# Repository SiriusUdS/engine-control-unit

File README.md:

# kicad-template
template for KiCad PCB projects

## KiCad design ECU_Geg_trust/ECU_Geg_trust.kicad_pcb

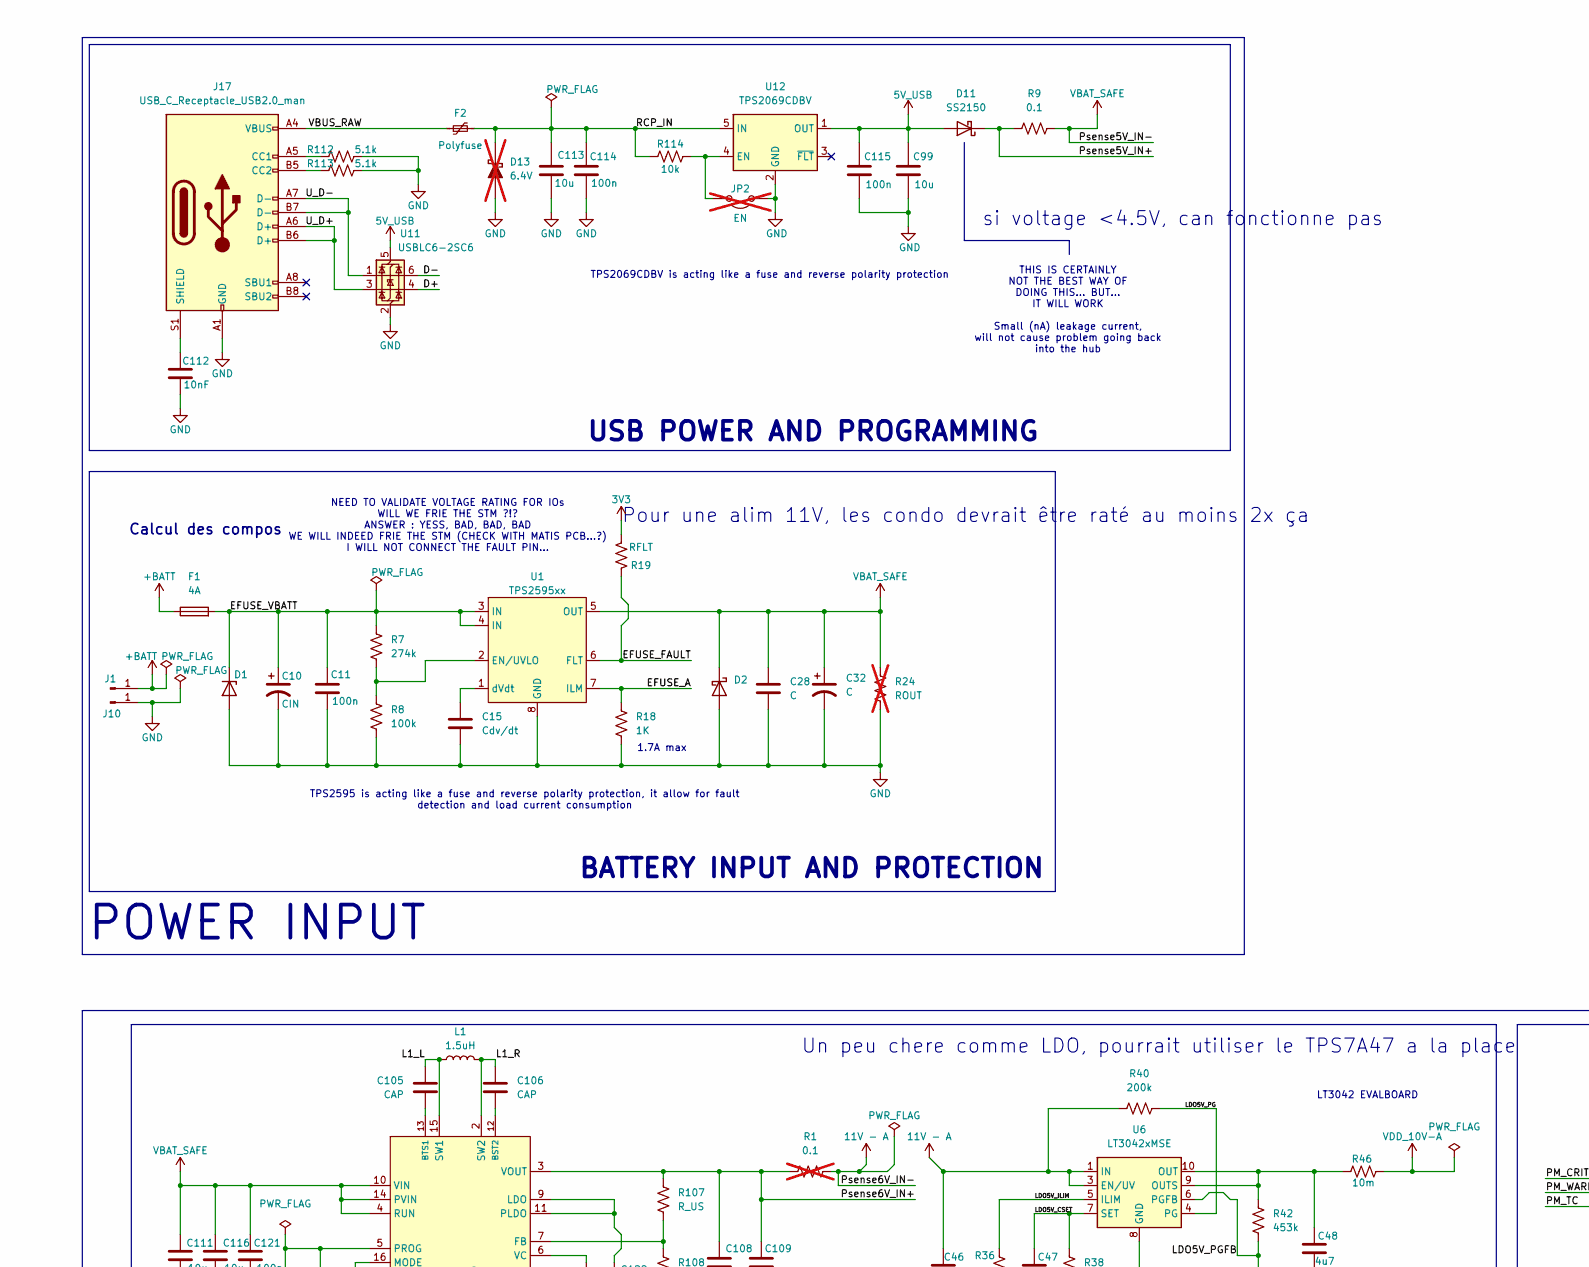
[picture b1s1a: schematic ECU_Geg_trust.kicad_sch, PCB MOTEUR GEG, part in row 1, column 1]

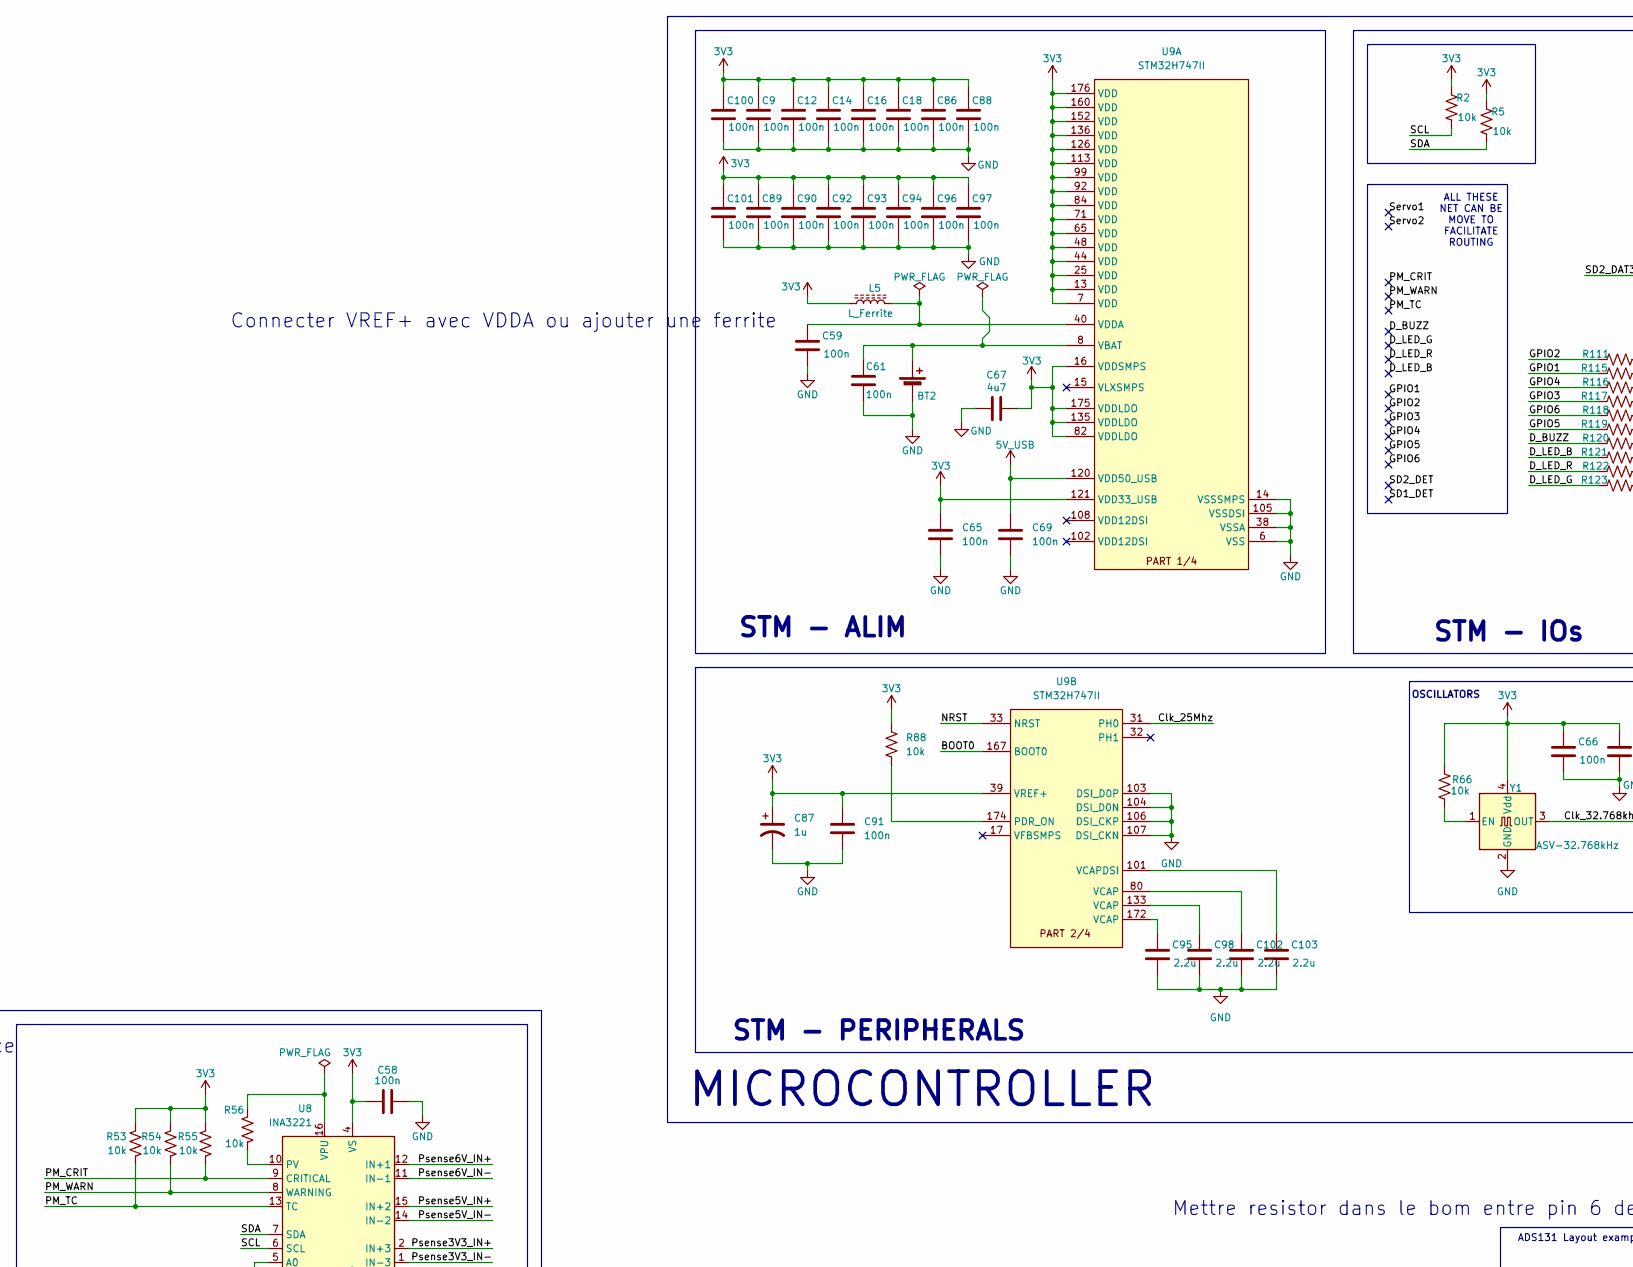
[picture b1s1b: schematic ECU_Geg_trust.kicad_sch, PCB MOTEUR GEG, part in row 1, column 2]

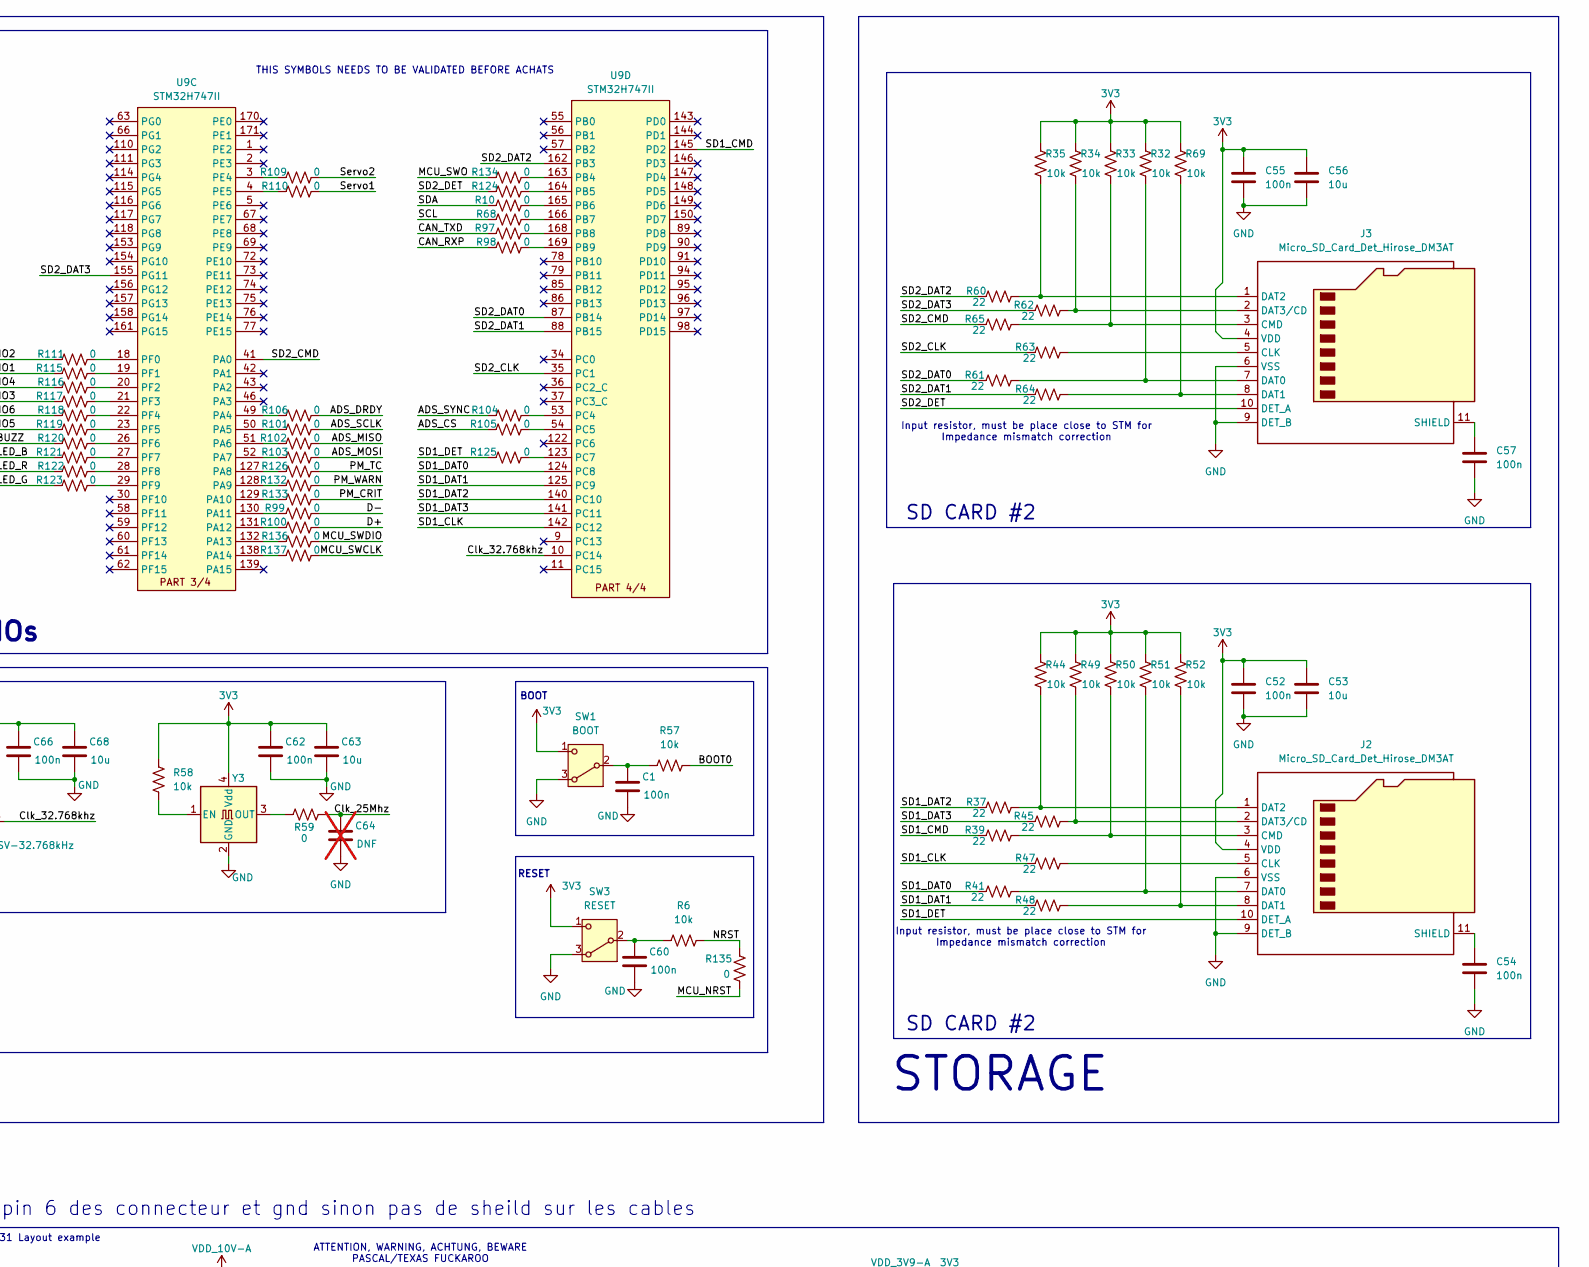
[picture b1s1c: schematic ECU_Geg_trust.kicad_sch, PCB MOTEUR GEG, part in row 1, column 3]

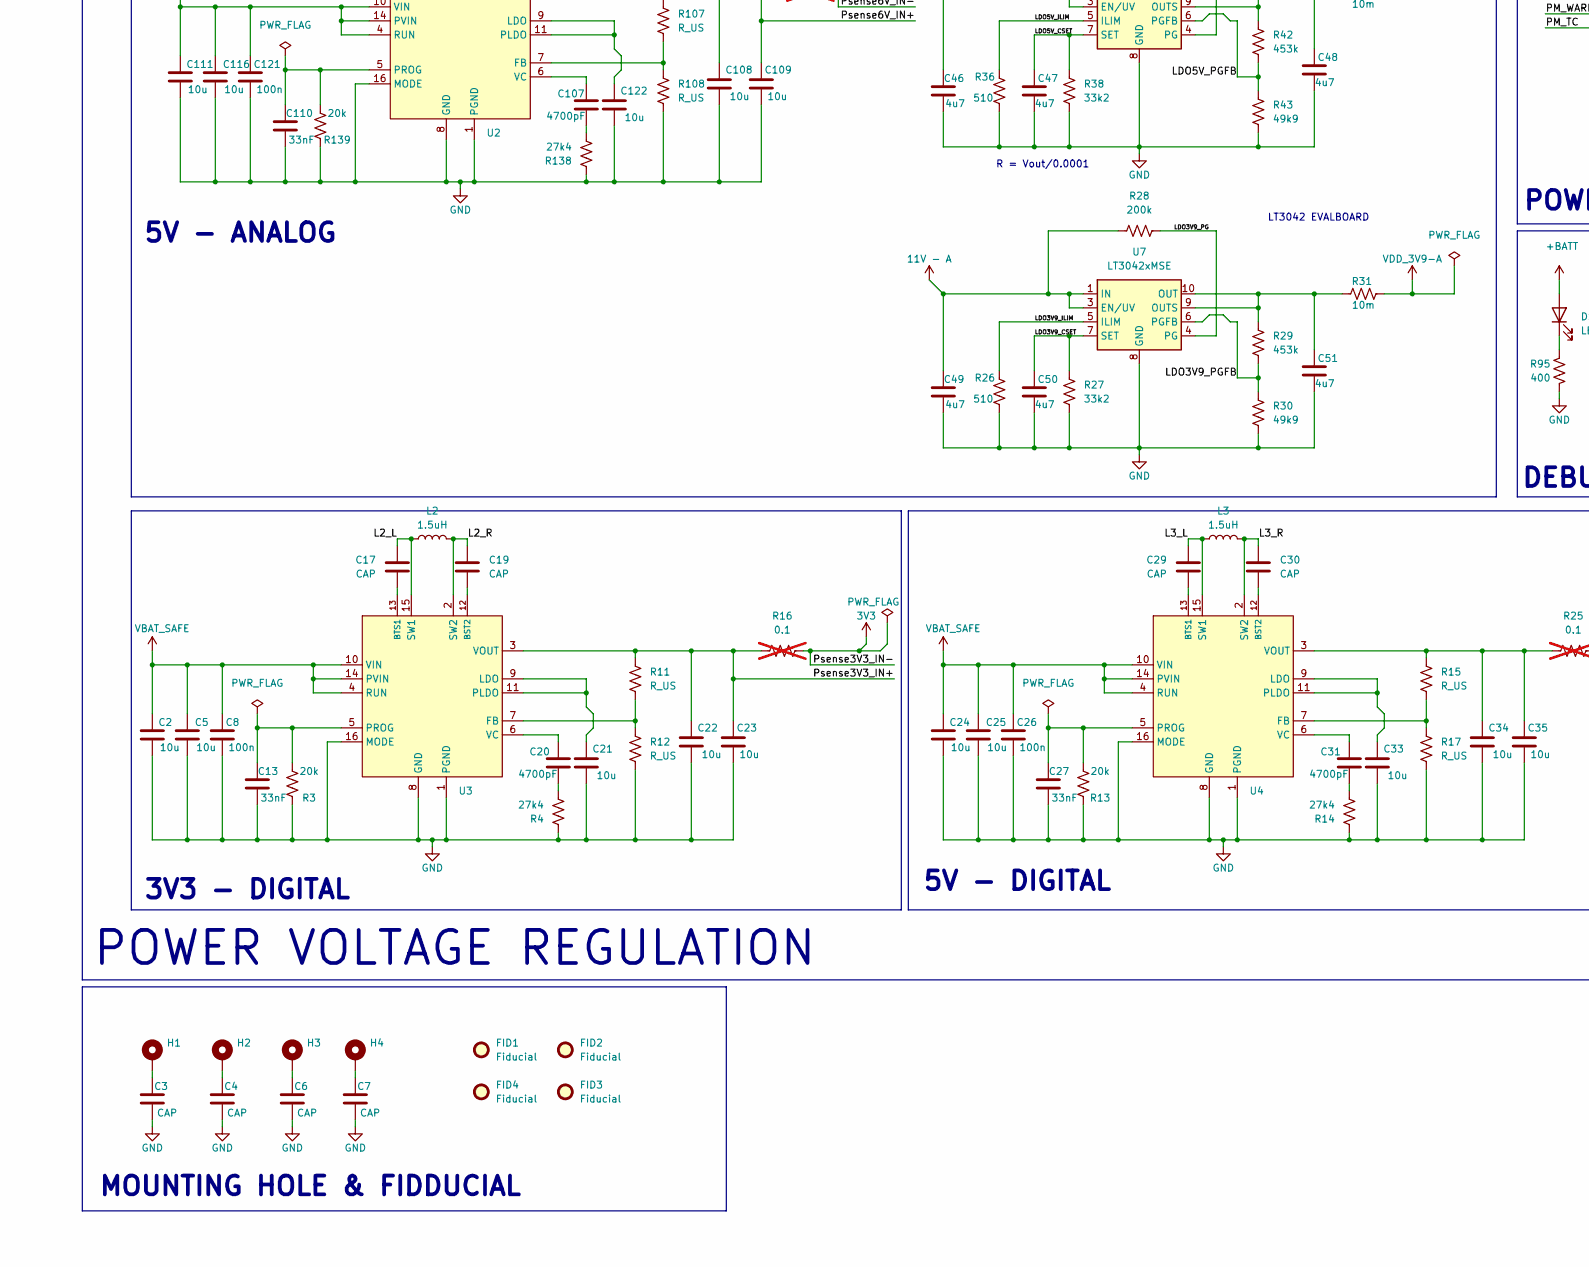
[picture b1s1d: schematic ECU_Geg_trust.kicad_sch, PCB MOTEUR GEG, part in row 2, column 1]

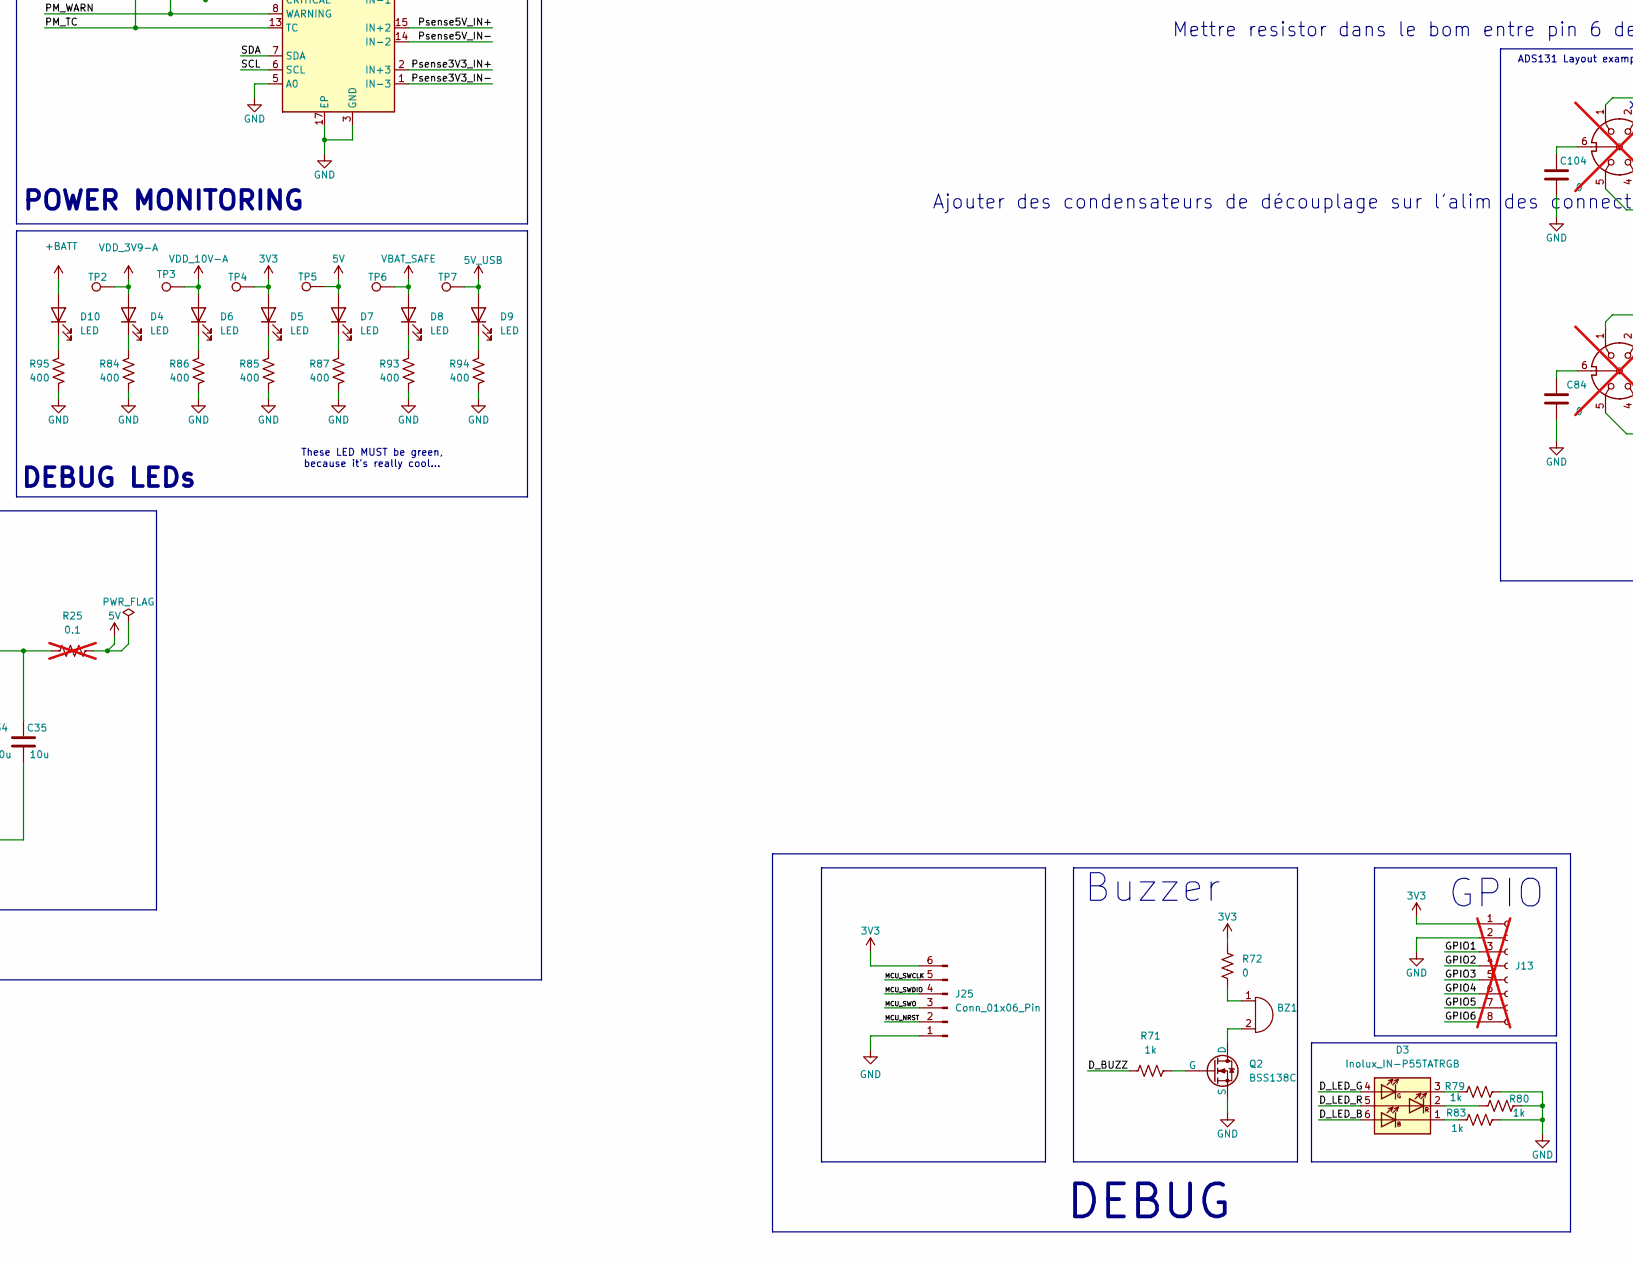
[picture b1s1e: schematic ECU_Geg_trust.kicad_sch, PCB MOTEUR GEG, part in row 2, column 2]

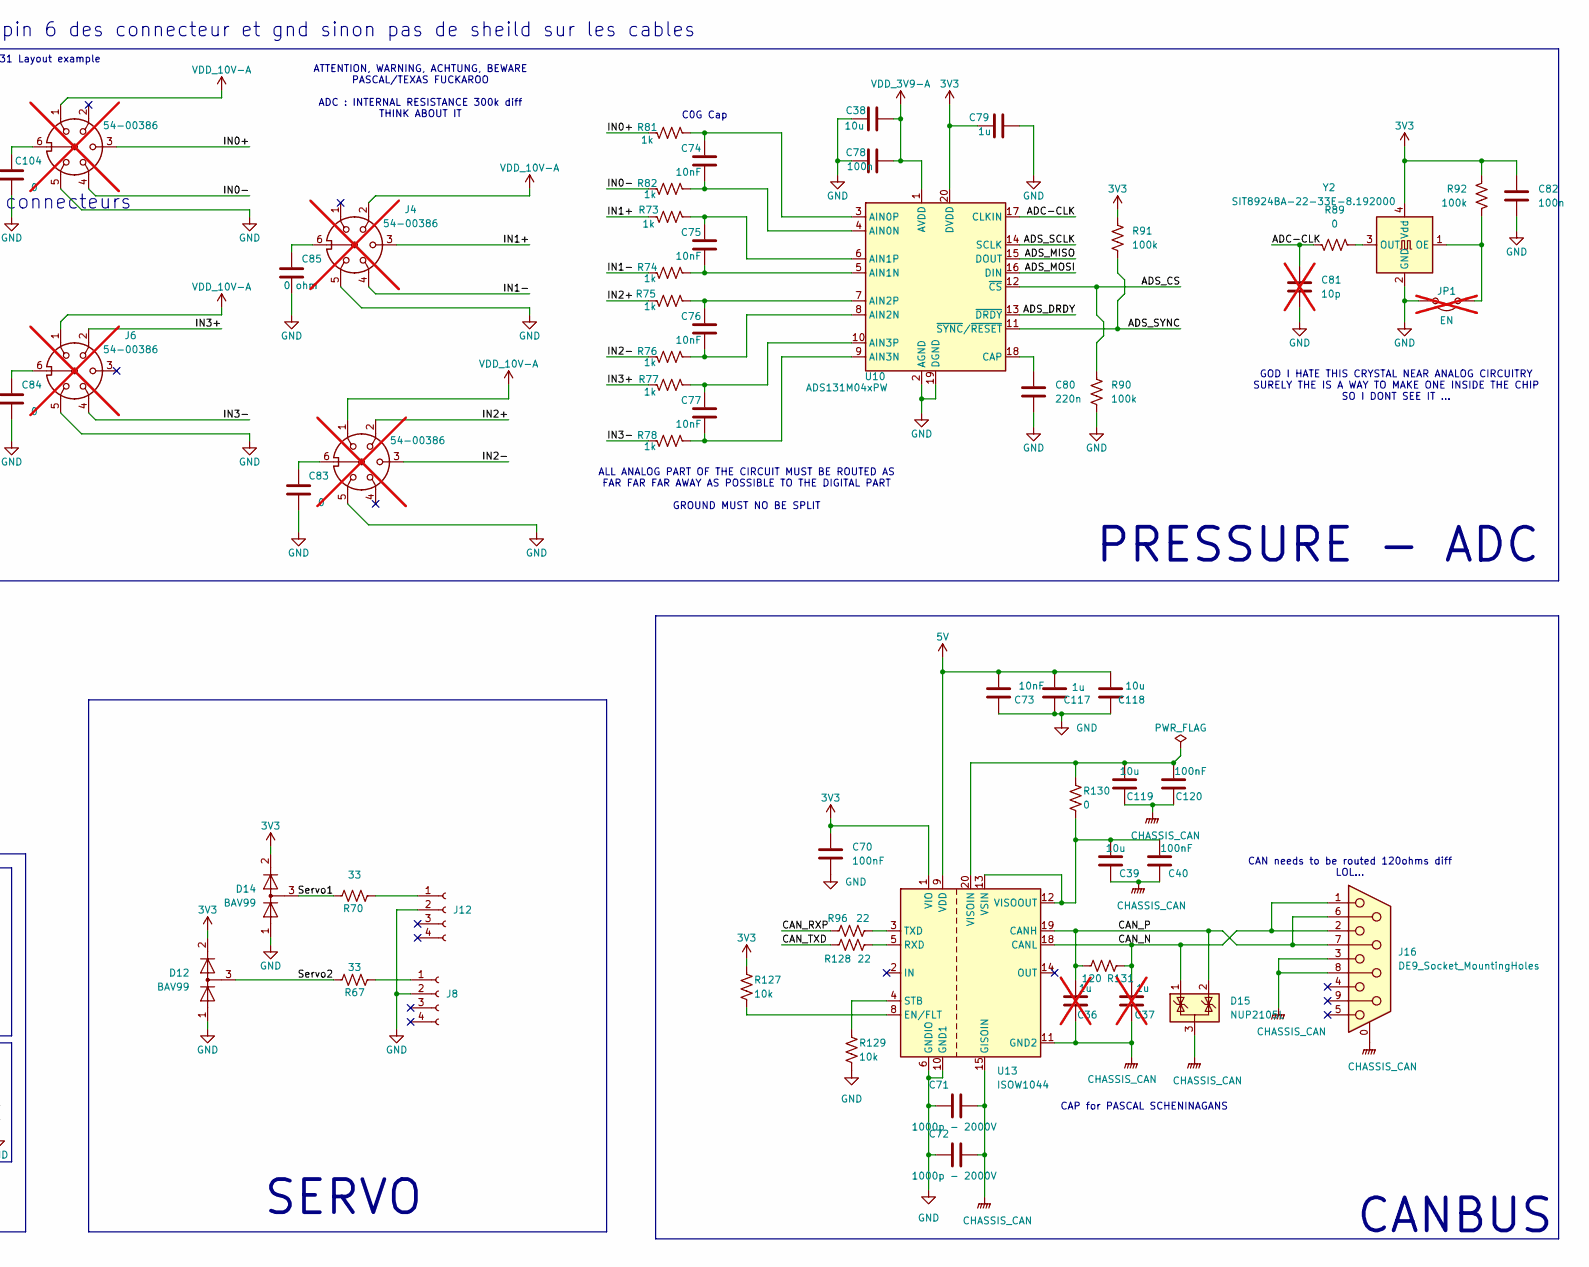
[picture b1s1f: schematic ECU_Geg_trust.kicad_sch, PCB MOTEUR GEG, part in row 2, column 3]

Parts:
BT2: Battery_Cell; BatteryHolder_Keystone_3000_1x12mm
BZ1: Buzzer_TDK_PS1240; Buzzer_Murata_PKMCS0909E; JLCP C910763
C1, C59, C60, C62, C65, C66, C69, C91: 100n; C_0402_1005Metric; JLCP C76997
C2, C23, C24, C35, C109, C111: 10u; C_1206_3216Metric; JLCP C1849
C3, C4, C6, C7, C17, C19, C29, C30, C105, C106: CAP; C_0402_1005Metric
C5, C21, C22, C25, C33, C34, C53, C56, C108, C116, C118, C122: 10u; C_0603_1608Metric; JLCP C70225
C8, C11, C26, C52, C54, C55, C57, C58, C61, C82, C121: 100n; C_0603_1608Metric; JLCP C1590
C9, C12, C14, C16, C18, C86, C88, C89, C90, C92, C93, C94, C96, C97, C100, C101, C114, C115: 100n; C_0402_1005Metric; Part Number 399-C0603C104K5RAC7411CT-ND; JLCP C76997
C10: CIN; CP_Elec_6.3x5.4
C13, C27, C110: 33nF; C_0402_1005Metric; JLCP C60425
C15: Cdv/dt; C_0603_1608Metric
C20, C31, C107: 4700pF; C_0402_1005Metric; JLCP C1538
C28: C; C_0603_1608Metric
C32: C; CP_Elec_6.3x5.4
C36, C37: 1u; C_0603_1608Metric; not fitted
C38: 10u; C_0805_2012Metric
C39, C119: 10u; C_0603_1608Metric; JLCP C1592
C40, C70, C120: 100nF; C_0603_1608Metric; JLCP C1590
C46, C47, C48, C49, C50, C51: 4u7; C_1206_3216Metric; JLCP C1872
C63, C68: 10u; C_0402_1005Metric; JLCP C77000
C64: DNF; C_0402_1005Metric; not fitted
C67: 4u7; C_0603_1608Metric; JLCP C23733
C71, C72: 1000p - 2000V; C_1210_3225Metric; JLCP C9196
C73, C74, C75, C76, C77, C112: 10nF; C_0603_1608Metric; JLCP C1589
C78: 100n; C_0603_1608Metric
C79, C117: 1u; C_0603_1608Metric; JLCP C1592
C80: 220n; C_0603_1608Metric; JLCP C1606
C81: 10p; C_0402_1005Metric; not fitted
C83, C84, C104: 0; C_0402_1005Metric; JLCP C17168
C85: 0 ohm; C_0402_1005Metric; JLCP C17168
C87: 1u; C_0402_1005Metric
C95, C98, C102, C103: 2.2u; C_0603_1608Metric; JLCP C23630
C99: 10u; C_0805_2012Metric; Part Number 399-C0603C104K5RAC7411CT-ND
C113: 10u; C_0603_1608Metric; Part Number 399-C0603C104K5RAC7411CT-ND; LCSC C1713
D1: SMBJ16A-13-F; D_SMB; JLCP C5353262
D2: MBR130T1G; D_SOD-123; JLCP C82461
D3: Inolux_IN-P55TATRGB; LED_Inolux_IN-P55TATRGB_PLCC6_5.0x5.5mm_P1.8mm; JLCP C5656598
D4, D5, D6, D7, D8, D9, D10: LED; LED_0603_1608Metric; JLCP C2286
D11: SS2150; D_SMA; JLCP C2891715
D12, D14: BAV99; SOT-23; JLCP C2500
D13: 6.4V; D_0603_1608Metric_Pad1.05x0.95mm_HandSolder; Part Number 1727-7327-1-ND; not fitted
D15: NUP2105L; SOT-23; JLCP C14486
F1: 4A; Fuse_0805_2012Metric; JLCP C187606
F2: Polyfuse; Fuse_0603_1608Metric_Pad1.05x0.95mm_HandSolder; Part Number 13-SMD0603B050TFCT-ND
FID1, FID2, FID3, FID4: Fiducial; Fiducial_0.5mm_Mask1mm
H1, H2, H3, H4: MountingHole_Pad; MountingHole_3.2mm_M3_DIN965_Pad_TopBottom
J1, J10: Conn_01x01_Pin; Wuerth_REDCUBE-THR_WP-THRBU_74650174_THR
J2, J3: Micro_SD_Card_Det_Hirose_DM3AT; microSD_HC_Hirose_DM3AT-SF-PEJM5; JLCP C114218
J4, J5, J7: 54-00386; not fitted
J6: 54-00386; JLCP C17168; not fitted
J8, J12: Conn_01x04_Socket; CUSTOM_CONN_1723102000_02_MOL
J13: Conn_01x08_Socket; PinHeader_2x04_P2.54mm_Vertical; not fitted
J16: DE9_Socket_MountingHoles; DSUB-9_Socket_Horizontal_P2.77x2.84mm_EdgePinOffset4.94mm_H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; JLCP C183530
J17: USB_C_Receptacle_USB2.0_man; USB_C_Receptacle_GCT_USB4105-xx-A_16P_TopMnt_Horizontal; Part Number 2073-USB4105-GF-ACT-ND; JLCP C5184243
J25: Conn_01x06_Pin; CUSTOM_Conn_JTAG
JP1, JP2: EN; C_0402_1005Metric; not fitted
L1, L2, L3: 1.5uH; CUSTOM_BMRA000606301R5MA1; JLCP C2936659 ps sur
L5: L_Ferrite; R_0402_1005Metric
Q2: BSS138C; TSOT-23_HandSoldering; JLCP C255592
R1, R16, R25: 0.1; R_0402_1005Metric; not fitted
R2, R5, R32, R33, R34, R35, R44, R49, R50, R51, R52, R53, R54, R55, R56, R69: 10k; R_0402_1005Metric; JLCP C25531
R3, R13, R139: 20k; R_0402_1005Metric; JLCP C25545
R4, R14, R138: 27k4; R_0402_1005Metric; JLCP C26971
R6, R57, R88, R127, R129: 10k; R_0603_1608Metric_Pad0.98x0.95mm_HandSolder; JLCP C15401
R7: 274k; R_0603_1608Metric
R8: 100k; R_0603_1608Metric
R9: 0.1; R_0402_1005Metric; JLCP C158960
R10, R59, R68, R89, R97, R98, R99, R100, R101, R102, R103, R104, R105, R106, R109, R110, R111, R115, R116, R117, R118, R119, R120, R121, R122, R123, R124, R125, R126, R132, R133, R134, R136, R137: 0; R_0402_1005Metric; JLCP C17168
R11, R12, R15, R17, R107, R108: R_US; R_0603_1608Metric
R18: 1K; R_0603_1608Metric
R19: RFLT; R_0603_1608Metric
R24: ROUT; R_0603_1608Metric; not fitted
R26, R36: 510; R_0603_1608Metric; JLCP C23193
R27, R38: 33k2; R_0603_1608Metric; JLCP C23003
R28, R40: 200k; R_0402_1005Metric; JLCP C25544
R29, R42: 453k; R_0603_1608Metric; JLCP C25818
R30, R43: 49k9; R_0603_1608Metric; JLCP C23184
R31, R46: 10m; R_0603_1608Metric; JLCP C156369
R37, R39, R41, R45, R47, R48, R60, R61, R62, R63, R64, R65, R96, R128: 22; R_0402_1005Metric; JLCP C159964
R58, R66: 10k; C_0402_1005Metric; JLCP C25531
R67, R70: 33; C_0603_1608Metric; JLCP C113041 ps sur
R71, R73, R74, R75, R76, R77, R78, R79, R80, R81, R82, R83: 1k; R_0603_1608Metric; JLCP C14676
R72: 0; R_0603_1608Metric; JLCP C15402
R84, R85, R86, R87, R93, R94, R95: 400; R_0402_1005Metric
R90, R91, R92: 100k; R_0402_1005Metric; JLCP C25530
R112, R113: 5.1k; R_0402_1005Metric; JLCP C25905
R114: 10k; R_0603_1608Metric; JLCP C15401
R130, R135: 0; R_0603_1608Metric_Pad0.98x0.95mm_HandSolder; JLCP C15402
R131: 120; R_0603_1608Metric_Pad0.98x0.95mm_HandSolder; JLCP C22787
SW1: BOOT; Nidec_Copal_CAS-120A; JLCP C2921537
SW3: RESET; Nidec_Copal_CAS-120A; JLCP C2921537
TP2, TP3, TP4, TP5, TP6, TP7: TestPoint; TestPoint_Pad_D2.5mm
U1: TPS2595xx; WSON-8-1EP_2x2mm_P0.5mm_EP0.9x1.6mm; JLCP C471038
U2, U3, U4: HTSSOP-16-1EP_4.4x5mm_P0.65mm_EP3.4x5mm_Mask2.46x2.31mm_The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; JLCP C580684 vr ps sur
U6, U7: LT3042xMSE; MSOP-10-1EP_3x3mm_P0.5mm_EP1.68x1.88mm
U8: INA3221; Texas_RGV0016A_VQFN-16-1EP_4x4mm_P0.65mm_EP2.1x2.1mm; JLCP C181255
U9: STM32H747II; LQFP-176_24x24mm_P0.5mm; JLCP C730199
U10: ADS131M04xPW; TSSOP-20_4.4x6.5mm_P0.65mm; JLCP C2862562
U11: USBLC6-2SC6; SOT-23-6; Part Number 497-5235-1-ND; JLCP C7519
U12: TPS2069CDBV; SOT-23-5; JLCP C181752
U13: ISOW1044; SOIC-20W_7.5x12.8mm_P1.27mm; JLCP C5216545
Y1: ASV-32.768kHz; Oscillator_SMD_Abracon_ASV-4Pin_7.0x5.1mm; JLCP ??
Y2: SIT8924BA-22-33E-8.192000; Oscillator_SMD_SiT_PQFN-4Pin_3.2x2.5mm; JLCP C7496633
Y3: ASV-25.000MHz; Oscillator_SMD_Abracon_ASV-4Pin_7.0x5.1mm; JLCP ??

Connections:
3V3: C9.1, C12.1, C14.1, C16.1, C18.1, C52.1, C53.1, C55.1, C56.1, C58.1, C62.1, C63.1, C65.1, C66.1, C67.2, C68.1, C70.1, C79.1, C82.2, C86.1, C87.1, C88.1, C89.1, C90.1, C91.1, C92.1, C93.1, C94.1, C96.1, C97.1, C100.1, C101.1, D5.2 (A), D12.2 (A), D14.2 (A), J2.4 (VDD), J3.4 (VDD), J13.1, J25.6, L5.1, R2.1, R5.1, R16.2, R19.2, R32.1, R33.1, R34.1, R35.1, R44.1, R49.1, R50.1, R51.1, R52.1, R53.1, R54.1, R55.1, R58.1, R66.1, R69.1, R72.1, R88.1, R91.1, R92.1, R127.1, SW1.1 (C), SW3.1 (C), TP4.1, U8.1 (IN-3), U8.4 (VS), U9.7 (VDD), U9.13 (VDD), U9.16 (VDDSMPS), U9.25 (VDD), U9.39 (VREF+), U9.44 (VDD), U9.48 (VDD), U9.65 (VDD), U9.71 (VDD), U9.82 (VDDLDO), U9.84 (VDD), U9.92 (VDD), U9.99 (VDD), U9.113 (VDD), U9.121 (VDD33_USB), U9.126 (VDD), U9.135 (VDDLDO), U9.136 (VDD), U9.152 (VDD), U9.160 (VDD), U9.175 (VDDLDO), U9.176 (VDD), U10.20 (DVDD), U13.1 (VIO), Y1.4 (Vdd), Y2.4 (Vdd), Y3.4 (Vdd)
5V: C73.2, C117.2, C118.2, D7.2 (A), R25.2, TP5.1, U13.9 (VDD)
5V_USB: C69.1, C99.1, C115.1, D9.2 (A), D11.2 (A), TP7.1, U9.120 (VDD50_USB), U11.5 (VBUS), U12.1 (OUT)
6V - A: C46.1, C49.1, R1.2, R28.1, R40.1, U6.1 (IN), U6.2 (IN), U6.3 (EN/UV), U7.1 (IN), U7.2 (IN), U7.3 (EN/UV), U8.11 (IN-1)
+BATT: D10.2 (A), F1.1, J1.1
/ADC-CLK: C81.2, R89.1, U10.17 (CLKIN)
/ADS_CS: R90.1, R105.1, U10.12 (~CS)
/ADS_DRDY: R106.2, U10.13 (~DRDY)
/ADS_MISO: R102.2, U10.15 (DOUT)
/ADS_MOSI: R103.2, U10.16 (DIN)
/ADS_SCLK: R101.2, U10.14 (SCLK)
/ADS_SYNC: R91.2, R104.1, U10.11 (~SYNC/~RESET)
/BOOT0: R57.2, U9.167 (BOOT0)
/CAN_N: C37.2, D15.1 (K), J16.1, J16.2, R131.1, U13.18 (CANL)
/CAN_P: C36.2, D15.2 (K), J16.6, J16.7, R131.2, U13.19 (CANH)
/CAN_RXP: R96.1, R98.1
/CAN_TXD: R97.1, R128.1
/Clk_25Mhz: C64.1, R59.2, U9.31 (PH0)
/Clk_32.768khz: U9.10 (PC14), Y1.3 (OUT)
/D+: R100.2, U11.4 (I/O2)
/D-: R99.2, U11.6 (I/O1)
/D_BUZZ: R71.1, R120.1
/D_LED_B: D3.6 (AB), R121.1
/D_LED_G: D3.4 (AG), R123.1
/D_LED_R: D3.5 (AR), R122.1
/EFUSE_A: R18.1, U1.7 (ILM)
/EFUSE_FAULT: R19.1, U1.6 (FLT)
/EFUSE_VBATT: C10.1, C11.1, D1.1 (K), F1.2, R7.1, U1.3 (IN), U1.4 (IN)
/GPIO1: J13.3, R115.1
/GPIO2: J13.4, R111.1
/GPIO3: J13.5, R117.1
/GPIO4: J13.6, R116.1
/GPIO5: J13.7, R119.1
/GPIO6: J13.8, R118.1
/IN0+: J5.3, R81.2
/IN0-: J5.4, R82.2
/IN1+: J4.3, R73.2
/IN1-: J4.4, R74.2
/IN2+: J7.2, R75.2
/IN2-: J7.3, R76.2
/IN3+: J6.2, R77.2
/IN3-: J6.4, R78.2
/L1_L: C105.1, L1.1, U2.15 (SW1)
/L1_R: C106.1, L1.2, U2.2 (SW2)
/L2_L: C17.1, L2.1, U3.15 (SW1)
/L2_R: C19.1, L2.2, U3.2 (SW2)
/L3_L: C29.1, L3.1, U4.15 (SW1)
/L3_R: C30.1, L3.2, U4.2 (SW2)
/LDO3V9_CSET: C50.1, R27.1, U7.7 (SET)
/LDO3V9_ILIM: R26.1, U7.5 (ILIM)
/LDO3V9_PG: R28.2, U7.4 (PG)
/LDO3V9_PGFB: R29.2, R30.1, U7.6 (PGFB)
/LDO5V_CSET: C47.1, R38.1, U6.7 (SET)
/LDO5V_ILIM: R36.1, U6.5 (ILIM)
/LDO5V_PG: R40.2, U6.4 (PG)
/LDO5V_PGFB: R42.2, R43.1, U6.6 (PGFB)
/MCU_NRST: J25.2, R135.1
/MCU_SWCLK: J25.5, R137.2
/MCU_SWDIO: J25.4, R136.2
/MCU_SWO: J25.3, R134.1
/NRST: R6.2, R135.2, U9.33 (NRST)
/PM_CRIT: R55.2, R133.2, U8.9 (CRITICAL)
/PM_TC: R53.2, R126.2, U8.13 (TC)
/PM_WARN: R54.2, R132.2, U8.8 (WARNING)
/Psense3V3_IN+: C22.1, C23.1, R11.1, R16.1, U3.3 (VOUT), U8.2 (IN+3)
/Psense5V_IN+: D11.1 (K), R9.1, U8.15 (IN+2)
/Psense6V_IN+: C108.1, C109.1, R1.1, R107.1, U2.3 (VOUT), U8.12 (IN+1)
/RCP_IN: C113.1, C114.1, D13.1 (K), F2.2, R114.1, U12.5 (IN)
/SCL: R2.2, R68.1, U8.6 (SCL)
/SD1_CLK: R47.1, U9.142 (PC12)
/SD1_CMD: R39.1, U9.145 (PD2)
/SD1_DAT0: R41.1, U9.124 (PC8)
/SD1_DAT1: R48.1, U9.125 (PC9)
/SD1_DAT2: R37.1, U9.140 (PC10)
/SD1_DAT3: R45.1, U9.141 (PC11)
/SD1_DET: J2.10 (DET_A), R125.1
/SD2_CLK: R63.1, U9.35 (PC1)
/SD2_CMD: R65.1, U9.41 (PA0)
/SD2_DAT0: R61.1, U9.87 (PB14)
/SD2_DAT1: R64.1, U9.88 (PB15)
/SD2_DAT2: R60.1, U9.162 (PB3)
/SD2_DAT3: R62.1, U9.155 (PG11)
/SD2_DET: J3.10 (DET_A), R124.1
/SDA: R5.2, R10.1, U8.7 (SDA)
/Servo1: D14.3 (K), R70.1, R110.2
/Servo2: D12.3 (K), R67.2, R109.2
/U_D+: J17.A6 (D+), J17.B6 (D+), U11.3 (I/O2)
/U_D-: J17.A7 (D-), J17.B7 (D-), U11.1 (I/O1)
/VBUS_RAW: F2.1, J17.A4 (VBUS), J17.A9 (VBUS), J17.B4 (VBUS), J17.B9 (VBUS)
CHASSIS_CAN: C36.1, C37.1, C39.1, C40.1, C71.2, C72.2, C119.1, C120.1, D15.3 (A), J16.0 (PAD), J16.3, J16.8, U13.11 (GND2), U13.15 (GISOIN), U13.16 (GISOIN), U13.17 (GISOIN)
GND: BT2.2 (-), C1.2, C2.2, C3.2, C4.2, C5.2, C6.2, C7.2, C8.2, C9.2, C10.2, C11.2, C12.2, C13.2, C14.2, C15.2, C16.2, C18.2, C21.2, C22.2, C23.2, C24.2, C25.2, C26.2, C27.2, C28.2, C32.2, C33.2, C34.2, C35.2, C38.1, C46.2, C47.2, C48.2, C49.2, C50.2, C51.2, C52.2, C53.2, C54.2, C55.2, C56.2, C57.2, C58.2, C59.2, C60.2, C61.1, C62.2, C63.2, C64.2, C65.2, C66.2, C67.1, C68.2, C69.2, C70.2, C71.1, C72.1, C73.1, C78.1, C79.2, C80.1, C81.1, C82.1, C83.2, C84.2, C85.2, C86.2, C87.2, C88.2, C89.2, C90.2, C91.2, C92.2, C93.2, C94.2, C95.2, C96.2, C97.2, C98.2, C99.2, C100.2, C101.2, C102.2, C103.2, C104.2, C108.2, C109.2, C110.2, C111.2, C112.2, C113.2, C114.2, C115.2, C116.2, C117.1, C118.1, C121.2, C122.2, D1.2 (A), D2.2 (A), D12.1 (K), D13.2 (A), D14.1 (K), J2.6 (VSS), J2.9 (DET_B), J3.6 (VSS), J3.9 (DET_B), J4.5, J5.5, J6.5, J7.5, J8.2, J10.1, J12.2, J13.2, J17.A1 (GND), J17.A12 (GND), J17.B1 (GND), J17.B12 (GND), J25.1, JP1.1 (A), JP2.1 (A), Q2.3 (S), R3.1, R4.1, R8.2, R12.2, R13.1, R14.1, R17.2, R18.2, R24.2, R26.2, R27.2, R30.2, R36.2, R38.2, R43.2, R79.2, R80.2, R83.2, R84.2, R85.2, R86.2, R87.2, R90.2, R93.2, R94.2, R95.2, R108.2, R112.1, R113.2, R129.2, R138.1, R139.1, SW1.3 (A), SW3.3 (A), U1.8 (GND), U1.9 (GND), U2.1 (PGND), U2.8 (GND), U2.16 (MODE), U3.1 (PGND), U3.8 (GND), U3.16 (MODE), U4.1 (PGND), U4.8 (GND), U4.16 (MODE), U6.8 (GND), U6.11 (GND), U7.8 (GND), U7.11 (GND), U8.3 (GND), U8.5 (A0), U8.17 (EP), U9.6 (VSS), U9.12 (VSS), U9.14 (VSSSMPS), U9.24 (VSS), U9.38 (VSSA), U9.45 (VSS), U9.47 (VSS), U9.64 (VSS), U9.70 (VSS), U9.81 (VSS), U9.83 (VSS), U9.93 (VSS), U9.100 (VSS), U9.103 (DSI_D0P), U9.104 (DSI_D0N), U9.105 (VSSDSI), U9.106 (DSI_CKP), U9.107 (DSI_CKN), U9.109 (VSSDSI), U9.112 (VSS), U9.119 (VSS), U9.134 (VSS), U9.137 (VSS), U9.151 (VSS), U9.159 (VSS), U9.173 (VSS), U10.2 (AGND), U10.19 (DGND), U11.2 (GND), U12.2 (GND), U13.6 (GNDIO), U13.10 (GND1), Y1.2 (GND), Y2.2 (GND), Y3.2 (GND)
unnamed: BT2.1 (+), C61.2, U9.8 (VBAT)
unnamed: BZ1.1, R72.2
unnamed: C3.1, H1.1
unnamed: C4.1, H2.1
unnamed: C6.1, H3.1
unnamed: C7.1, H4.1
unnamed: C20.1, R4.2
unnamed: C31.1, R14.2
unnamed: C83.1, J7.6, J7.SH
unnamed: C84.1, J6.6, J6.SH
unnamed: C85.1, J4.6, J4.SH
unnamed: C95.1, U9.172 (VCAP)
unnamed: C98.1, U9.133 (VCAP)
unnamed: C102.1, U9.80 (VCAP)
unnamed: C104.1, J5.6, J5.SH
unnamed: C107.1, R138.2
unnamed: D3.1 (KB), R83.1
unnamed: D3.3 (KG), R79.1
unnamed: D3.2 (KR), R80.1
unnamed: D4.1 (K), R84.1
unnamed: D5.1 (K), R85.1
unnamed: D6.1 (K), R86.1
unnamed: D7.1 (K), R87.1
unnamed: D8.1 (K), R93.1
unnamed: D9.1 (K), R94.1
unnamed: D10.1 (K), R95.1
unnamed: J2.5 (CLK), R47.2
unnamed: J2.3 (CMD), R39.2, R50.2
unnamed: J2.7 (DAT0), R41.2, R51.2
unnamed: J2.8 (DAT1), R48.2, R52.2
unnamed: J2.1 (DAT2), R37.2, R44.2
unnamed: J2.2 (DAT3/CD), R45.2, R49.2
unnamed: C54.1, J2.11 (SHIELD)
unnamed: J3.5 (CLK), R63.2
unnamed: J3.3 (CMD), R33.2, R65.2
unnamed: J3.7 (DAT0), R32.2, R61.2
unnamed: J3.8 (DAT1), R64.2, R69.2
unnamed: J3.1 (DAT2), R35.2, R60.2
unnamed: J3.2 (DAT3/CD), R34.2, R62.2
unnamed: C57.1, J3.11 (SHIELD)
unnamed: J8.1, R67.1
unnamed: J12.1, R70.2
unnamed: J17.A5 (CC1), R112.2
unnamed: J17.B5 (CC2), R113.1
unnamed: C112.1, J17.S1 (SHIELD)
unnamed: JP1.2 (B), R92.2, Y2.1 (OE)
unnamed: JP2.2 (B), R114.2, U12.4 (EN)
unnamed: BZ1.2, Q2.1 (D)
unnamed: Q2.2 (G), R71.2
unnamed: C1.1, R57.1, SW1.2 (B)
unnamed: C60.1, R6.1, SW3.2 (B)
unnamed: R7.2, R8.1, U1.2 (EN/UVLO)
unnamed: C15.1, U1.1 (dVdt)
unnamed: C106.2, U2.12 (BST2)
unnamed: C105.2, U2.13 (BTS1)
unnamed: R107.2, R108.1, U2.7 (FB)
unnamed: C122.1, U2.9 (LDO), U2.11 (PLDO)
unnamed: C110.1, R139.2, U2.5 (PROG)
unnamed: C107.2, U2.6 (VC)
unnamed: C19.2, U3.12 (BST2)
unnamed: C17.2, U3.13 (BTS1)
unnamed: R11.2, R12.1, U3.7 (FB)
unnamed: C21.1, U3.9 (LDO), U3.11 (PLDO)
unnamed: C13.1, R3.2, U3.5 (PROG)
unnamed: C20.2, U3.6 (VC)
unnamed: C30.2, U4.12 (BST2)
unnamed: C29.2, U4.13 (BTS1)
unnamed: R15.2, R17.1, U4.7 (FB)
unnamed: C33.1, U4.9 (LDO), U4.11 (PLDO)
unnamed: C27.1, R13.2, U4.5 (PROG)
unnamed: C31.2, U4.6 (VC)
unnamed: C34.1, C35.1, R15.1, R25.1, U4.3 (VOUT)
unnamed: C48.1, R42.1, R46.1, U6.9 (OUTS), U6.10 (OUT)
unnamed: C51.1, R29.1, R31.1, U7.9 (OUTS), U7.10 (OUT)
unnamed: R56.2, U8.10 (PV)
unnamed: R56.1, U8.16 (VPU)
unnamed: C59.1, L5.2, U9.40 (VDDA)
unnamed: R88.2, U9.174 (PDR_ON)
unnamed: C103.1, U9.101 (VCAPDSI)
unnamed: R106.1, U9.49 (PA4)
unnamed: R101.1, U9.50 (PA5)
unnamed: R102.1, U9.51 (PA6)
unnamed: R103.1, U9.52 (PA7)
unnamed: R126.1, U9.127 (PA8)
unnamed: R132.1, U9.128 (PA9)
unnamed: R133.1, U9.129 (PA10)
unnamed: R99.1, U9.130 (PA11)
unnamed: R100.1, U9.131 (PA12)
unnamed: R136.1, U9.132 (PA13)
unnamed: R137.1, U9.138 (PA14)
unnamed: R109.1, U9.3 (PE4)
unnamed: R110.1, U9.4 (PE5)
unnamed: R111.2, U9.18 (PF0)
unnamed: R115.2, U9.19 (PF1)
unnamed: R116.2, U9.20 (PF2)
unnamed: R117.2, U9.21 (PF3)
unnamed: R118.2, U9.22 (PF4)
unnamed: R119.2, U9.23 (PF5)
unnamed: R120.2, U9.26 (PF6)
unnamed: R121.2, U9.27 (PF7)
unnamed: R122.2, U9.28 (PF8)
unnamed: R123.2, U9.29 (PF9)
unnamed: R134.2, U9.163 (PB4)
unnamed: R124.2, U9.164 (PB5)
unnamed: R10.2, U9.165 (PB6)
unnamed: R68.2, U9.166 (PB7)
unnamed: R97.2, U9.168 (PB8)
unnamed: R98.2, U9.169 (PB9)
unnamed: R104.2, U9.53 (PC4)
unnamed: R105.2, U9.54 (PC5)
unnamed: R125.2, U9.123 (PC7)
unnamed: C74.1, R82.1, U10.4 (AIN0N)
unnamed: C74.2, R81.1, U10.3 (AIN0P)
unnamed: C75.1, R74.1, U10.5 (AIN1N)
unnamed: C75.2, R73.1, U10.6 (AIN1P)
unnamed: C76.1, R76.1, U10.8 (AIN2N)
unnamed: C76.2, R75.1, U10.7 (AIN2P)
unnamed: C77.1, R78.1, U10.9 (AIN3N)
unnamed: C77.2, R77.1, U10.10 (AIN3P)
unnamed: C80.2, U10.18 (CAP)
unnamed: R127.2, U13.8 (EN/FLT)
unnamed: R128.2, U13.5 (RXD)
unnamed: R129.1, U13.4 (STB)
unnamed: R96.2, U13.3 (TXD)
unnamed: C119.2, C120.2, R130.1, U13.20 (VISOIN)
unnamed: C39.2, C40.2, R130.2, U13.12 (VISOOUT), U13.13 (VSIN)
unnamed: R66.2, Y1.1 (EN)
unnamed: R89.2, Y2.3 (OUT)
unnamed: R58.2, Y3.1 (EN)
unnamed: R59.1, Y3.3 (OUT)
VBAT_SAFE: C2.1, C5.1, C8.1, C24.1, C25.1, C26.1, C28.1, C32.1, C111.1, C116.1, C121.1, D2.1 (K), D8.2 (A), R9.2, R24.1, TP6.1, U1.5 (OUT), U2.4 (RUN), U2.10 (VIN), U2.14 (PVIN), U3.4 (RUN), U3.10 (VIN), U3.14 (PVIN), U4.4 (RUN), U4.10 (VIN), U4.14 (PVIN), U8.14 (IN-2)
VDD_3V9-A: C38.2, C78.2, D4.2 (A), R31.2, TP2.1, U10.1 (AVDD)
VDD_5V-A: D6.2 (A), J4.2, J5.1, J6.1, J7.1, R46.2, TP3.1

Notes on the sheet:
CAN needs to be routed 120ohms diff LOL...
DEBUG LEDs
POWER VOLTAGE REGULATION
STM - ALIM
THIS SYMBOLS NEEDS TO BE VALIDATED BEFORE ACHATS
Buzzer
BOOT
si voltage <4.5V, can fonctionne pas
Connecter VREF+ avec VDDA ou ajouter une ferrite
USB POWER AND PROGRAMMING
ATTENTION, WARNING, ACHTUNG, BEWARE PASCAL/TEXAS FUCKAROO ADC : INTERNAL RESISTANCE 300k diff THINK ABOUT IT
MOUNTING HOLE & FIDDUCIAL
C0G Cap
BATTERY INPUT AND PROTECTION
POWER INPUT
POWER MONITORING
LT3042 EVALBOARD
THIS IS CERTAINLY NOT THE BEST WAY OF DOING THIS... BUT... IT WILL WORK Small (nA) leakage current, will not cause problem going back into the hub
STORAGE
Pour une alim 11V, les condo devrait être raté au moins 2x ça
SD CARD #2
3V3 - DIGITAL
NEED TO VALIDATE VOLTAGE RATING FOR IOs WILL WE FRIE THE STM ?!? ANSWER : YESS, BAD, BAD, BAD WE WILL INDEED FRIE THE STM (CHECK WITH MATIS PCB...?) I WILL NOT CONNECT THE FAULT PIN...
STM - PERIPHERALS
5V - DIGITAL
5V - ANALOG
OSCILLATORS
GOD I HATE THIS CRYSTAL NEAR ANALOG CIRCUITRY SURELY THE IS A WAY TO MAKE ONE INSIDE THE CHIP SO I DONT SEE IT ...
Calcul des compos
STM - IOs
Input resistor, must be place close to STM for Impedance mismatch correction
These LED MUST be green, because it's really cool...
TPS2595 is acting like a fuse and reverse polarity protection, it allow for fault detection and load current consumption
CAP for PASCAL SCHENINAGANS
DEBUG
CANBUS
RESET
PRESSURE - ADC
ALL THESE NET CAN BE MOVE TO FACILITATE ROUTING
GPIO
